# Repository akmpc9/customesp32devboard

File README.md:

# customesp32devboard
# Custom ESP32-S3 Dev Board (v1)

A custom **ESP32-S3** development board designed to be **reliable**, **good-quality**, and **feature-rich** for **learning + teaching electronics** (power, USB, routing, GPIO, LEDs/buttons, battery monitoring).

---

## Images

---

## Project goals

- Make a **robust ESP32-S3 platform** (clean power + clean layout)
- Break out lots of GPIO for experiments
- Add useful learning features (LEDs, buttons, battery sense, USB programming)
- Be easy to reproduce and improve (v1 → v2)

---

## Key features (v1)

- **ESP32-S3-WROOM-1** module (Wi-Fi + BLE)
- **USB-C** connector
- **CH340C** USB-UART for flashing/serial
- **5V → 3.3V buck converter** (efficient vs linear regulators)
- **Auto-program** support (EN/BOOT control from USB-UART)
- **GPIO headers** for prototyping
- **User button** + indicator LEDs
- **Battery sense divider** (read VBAT on an ADC pin)
- Layout rules applied: antenna keepout, USB routing, buck SW isolation, ground plane

---

## Flashing / serial

- Plug USB-C into your PC
- Select the **CH340** COM port
- Use Arduino IDE or PlatformIO (ESP32-S3 target)

---

## BOM (JLCPCB Assembly Order)
I removed the esp32 chip and the leds for a more economical PCBA.

**Build qty:** 5 PCBs (inferred from U1/U2/U3/J1 qty = 5)  
**Parts cost (from JLC export, parts only):** **$60.8676** (assembly + PCB + shipping not included)

Legend: 🟦 Basic | 🟧 Extended | ⚠️ Check

---

<details open>
<summary><b>MCU</b></summary>

| Designators | Qty | Value | Footprint | LCSC | Manufacturer | Lib | Link | Notes |
|---|---:|---|---|---|---|---|---|---|
| U1 | 5 | ESP32-S3-WROOM-1 | RF_Module:ESP32-S3-WROOM-1 | C2913202 | Espressif Systems | 🟧 | https://jlcpcb.com/partdetail/3198300-ESP32_S3_WROOM_1N16R8/C2913202 | ⚠️ Comment mismatch in export |
</details>

<details open>
<summary><b>USB / Interface</b></summary>

| Designators | Qty | Value | Footprint | LCSC | Manufacturer | Lib | Link | Notes |
|---|---:|---|---|---|---|---|---|---|
| J1 | 5 | TYPE-C-31-M-12 | TYPE-C-31-M-12:HRO_TYPE-C-31-M-12 | C165948 | Korean Hroparts Elec | 🟧 | https://jlcpcb.com/partdetail/Korean_HropartsElec-TYPE_C_31_M12/C165948 |  |
| U2 | 5 | CH340C | Package_SO:SOIC-16_3.9x9.9mm_P1.27mm | C7464026 | WCH(Jiangsu Qin Heng) | 🟧 | https://jlcpcb.com/partdetail/WCH_Jiangsu_Qin_Heng-CH340C/C7464026 |  |
| D2,D3,D4 | 21 | LESD5D5.0CT1G | LESD5D5.0CT1G:TVS_LESD5D5.0CT1G | C5199850 | UMW(Youtai) | 🟧 | https://jlcpcb.com/partdetail/5885882-LESD5D5_0CT1G_UMW/C5199850 | ⚠️ Comment mismatch in export |
</details>

<details open>
<summary><b>Power (Buck)</b></summary>

| Designators | Qty | Value | Footprint | LCSC | Manufacturer | Lib | Link | Notes |
|---|---:|---|---|---|---|---|---|---|
| U3 | 5 | MP2303ADN | Package_SO:SOIC-8-1EP_3.9x4.9mm_P1.27mm_EP2.62x3.51mm | C18876 | Monolithic Power Systems | 🟧 | https://jlcpcb.com/partdetail/19579-MP2303ADN_LFZ/C18876 |  |
| L1 | 9 | 4.7uH | Inductor_SMD:L_Sunlord_SWPA4012S | C316363 | Sunlord | 🟧 | https://jlcpcb.com/partdetail/Sunlord-SWPA4012S4R7MT/C316363 |  |
| D1 | 15 | 1N5819HW-7-F | Diode_SMD:D_SOD-123 | C82544 | Diodes Incorporated | 🟧 | https://jlcpcb.com/partdetail/DiodesIncorporated-1N5819HW_7F/C82544 |  |
| RTOP1 | 20 | 26.1k | Resistor_SMD:R_0603_1608Metric | C325725 | TyoHM | 🟧 | https://jlcpcb.com/partdetail/TyoHM-RMC060326_1K1N/C325725 | ⚠️ Comment mismatch in export |
| RCOMP1 | 20 | 12k | Resistor_SMD:R_0603_1608Metric | C22790 | UNI-ROYAL | 🟦 | https://jlcpcb.com/partdetail/23517-0603WAF1202T5E/C22790 |  |
| CCOMP1 | 20 | 3.9nF | Capacitor_SMD:C_0603_1608Metric | C1618 | FH | 🟧 | https://jlcpcb.com/partdetail/1970-0603B392K500NT/C1618 |  |
| CSS1 | 20 | 10nF | Capacitor_SMD:C_0603_1608Metric | C57112 | FH | 🟦 | https://jlcpcb.com/partdetail/58143-0603B103K500NT/C57112 |  |
</details>

<details open>
<summary><b>Passives (Caps)</b></summary>

| Designators | Qty | Value | Footprint | LCSC | Manufacturer | Lib | Link | Notes |
|---|---:|---|---|---|---|---|---|---|
| C1 | 20 | 1uF | Capacitor_SMD:C_0603_1608Metric | C15849 | Samsung EM | 🟦 | https://jlcpcb.com/partdetail/16531-CL10A105KB8NNNC/C15849 |  |
| C2,C4,C6,CBST1,CCH340C1,CCH340C2,CIN2,CLED1,CLED2 | 55 | 100nF | Capacitor_SMD:C_0603_1608Metric | C14663 | YAGEO | 🟦 | https://jlcpcb.com/partdetail/YAGEO-CC0603KRX7R9BB104/C14663 | ⚠️ “multiple types” warning in export |
| C3,CIN1,COUT1,COUT2 | 24 | 22uF | Capacitor_SMD:C_1206_3216Metric | C12891 | Samsung EM | 🟦 | https://jlcpcb.com/partdetail/13537-CL31A226KAHNNNE/C12891 | ⚠️ “multiple types” warning in export |
| C5 | 20 | 10uF | Capacitor_SMD:C_0603_1608Metric | C19702 | Samsung EM | 🟦 | https://jlcpcb.com/partdetail/20411-CL10A106KP8NNNC/C19702 |  |
</details>

<details open>
<summary><b>Passives (Resistors)</b></summary>

| Designators | Qty | Value | Footprint | LCSC | Manufacturer | Lib | Link | Notes |
|---|---:|---|---|---|---|---|---|---|
| R1,R2 | 20 | 5k1 | Resistor_SMD:R_0603_1608Metric | C23186 | UNI-ROYAL | 🟦 | https://jlcpcb.com/partdetail/23913-0603WAF5101T5E/C23186 | ⚠️ Comment mismatch in export |
| R3,R7 | 20 | 10k | Resistor_SMD:R_0805_2012Metric | C17414 | UNI-ROYAL | 🟦 | https://jlcpcb.com/partdetail/18102-0805W8F1002T5E/C17414 | ⚠️ Comment mismatch in export |
| R5,R6 | 20 | 4.7k | Resistor_SMD:R_0603_1608Metric | C23162 | UNI-ROYAL | 🟦 | https://jlcpcb.com/partdetail/23889-0603WAF4701T5E/C23162 | ⚠️ Comment mismatch in export |
| R8,R9,R12,RBOT1 | 30 | 10k | Resistor_SMD:R_0603_1608Metric | C25804 | UNI-ROYAL | 🟦 | https://jlcpcb.com/partdetail/26547-0603WAF1002T5E/C25804 | ⚠️ Warnings in export |
| R10,R11 | 20 | 100k | Resistor_SMD:R_0603_1608Metric | C25803 | UNI-ROYAL | 🟦 | https://jlcpcb.com/partdetail/26546-0603WAF1003T5E/C25803 | ⚠️ Comment mismatch in export |
| RLED1,RLED2 | 20 | 330R | Resistor_SMD:R_0603_1608Metric | C23138 | UNI-ROYAL | 🟦 | https://jlcpcb.com/partdetail/23865-0603WAF3300T5E/C23138 | ⚠️ Use **330R** in BOM to avoid LED auto-match |
| RLED3 | 20 | 3.3k | Resistor_SMD:R_0603_1608Metric | C22978 | UNI-ROYAL | 🟦 | https://jlcpcb.com/partdetail/23705-0603WAF3301T5E/C22978 |  |
</details>

<details open>
<summary><b>LEDs / Indicators</b></summary>

| Designators | Qty | Value | Footprint | LCSC | Manufacturer | Lib | Link | Notes |
|---|---:|---|---|---|---|---|---|---|
| D5,D6 | 12 | SK6805 | LED_SMD:LED_SK6805_PLCC4_2.4x2.7mm_P1.3mm | C2890035 | OPSCO | 🟧 | https://jlcpcb.com/partdetail/OPSCOOptoelectronics-SK6805EC15/C2890035 | ⚠️ Comment mismatch in export |
| D7 | 20 | SM0603UYC | SM0603UYC:LED_SM0603UYC | C2287 | Hubei KENTO | 🟧 | https://jlcpcb.com/partdetail/Hubei_KENTOElec-KT0603Y/C2287 | ⚠️ Comment mismatch in export |
</details>

<details open>
<summary><b>Discrete / Switches</b></summary>

| Designators | Qty | Value | Footprint | LCSC | Manufacturer | Lib | Link | Notes |
|---|---:|---|---|---|---|---|---|---|
| Q1,Q2 | 15 | MMBT3904 | Package_TO_SOT_SMD:SOT-23 | C7420353 | hongjiacheng | 🟧 | https://jlcpcb.com/partdetail/hongjiacheng-MMBT3904/C7420353 |  |
| S1,S2,S3 | 19 | TS-1088-AR02016 | TS-1088-AR02016:SW_TS-1088-AR02016 | C720477 | XUNPU | 🟦 | https://jlcpcb.com/partdetail/XUNPU-TS_1088AR02016/C720477 |  |
</details>

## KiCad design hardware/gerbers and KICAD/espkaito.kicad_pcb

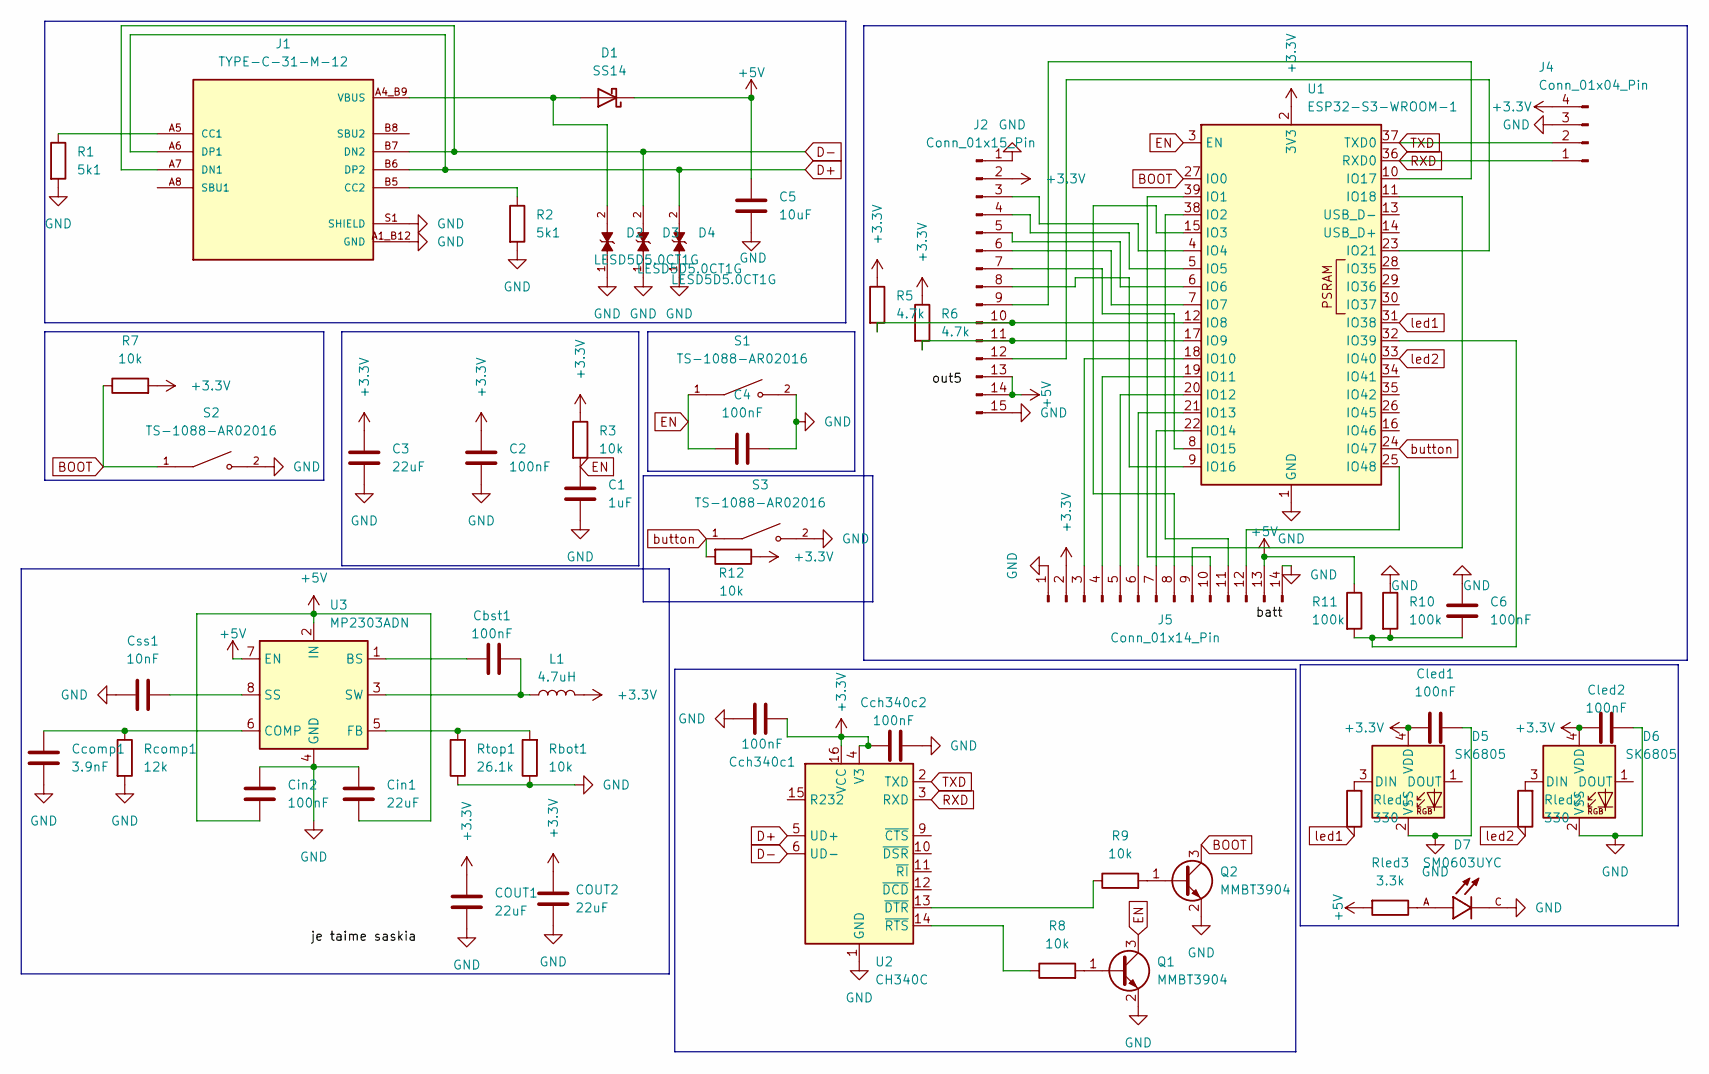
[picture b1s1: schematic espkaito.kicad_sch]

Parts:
C1: 1uF; C_0603_1608Metric
C2, C4, C6: 100nF; C_0603_1608Metric
C3: 22uF; C_1206_3216Metric
C5: 10uF; C_0603_1608Metric
COUT1, COUT2: 22uF; C_1206_3216Metric
Cbst1: 100nF; C_0603_1608Metric
Cch340c1, Cch340c2: 100nF; C_0603_1608Metric
Ccomp1: 3.9nF; C_0603_1608Metric
Cin1: 22uF; C_1206_3216Metric
Cin2: 100nF; C_0603_1608Metric
Cled1, Cled2: 100nF; C_0603_1608Metric
Css1: 10nF; C_0603_1608Metric
D1: SS14; D_SMA
D2, D3, D4: LESD5D5.0CT1G; TVS_LESD5D5.0CT1G; PARTREV O
D5, D6: SK6805; LED_SK6805_PLCC4_2.4x2.7mm_P1.3mm
D7: SM0603UYC; LED_SM0603UYC; PARTREV A
J1: TYPE-C-31-M-12; HRO_TYPE-C-31-M-12; PARTREV 2020.12.08
J2: Conn_01x15_Pin; PinHeader_1x15_P2.54mm_Vertical
J4: Conn_01x04_Pin; PinHeader_1x04_P2.54mm_Vertical
J5: Conn_01x14_Pin; PinHeader_1x14_P2.54mm_Vertical
L1: 4.7uH; L_Sunlord_SWPA4012S
Q1, Q2: MMBT3904; SOT-23
R1, R2: 5k1; R_0603_1608Metric
R3, R7: 10k; R_0805_2012Metric
R5, R6: 4.7k; R_0603_1608Metric
R8, R9, R12: 10k; R_0603_1608Metric
R10, R11: 100k; R_0603_1608Metric
Rbot1: 10k; R_0603_1608Metric
Rcomp1: 12k; R_0603_1608Metric
Rled1, Rled2: 330; R_0603_1608Metric
Rled3: 3.3k; R_0603_1608Metric
Rtop1: 26.1k; R_0603_1608Metric
S1, S2, S3: TS-1088-AR02016; SW_TS-1088-AR02016; PARTREV N/A
U1: ESP32-S3-WROOM-1
U2: CH340C; SOIC-16_3.9x9.9mm_P1.27mm
U3: MP2303ADN; SOIC-8-1EP_3.9x4.9mm_P1.27mm_EP2.62x3.51mm_ThermalVias

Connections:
+3.3V: C2.1, C3.1, COUT1.1, COUT2.1, Cch340c1.2, Cch340c2.2, Cled1.2, Cled2.2, D5.4 (VDD), D6.4 (VDD), J2.2, J4.4, J5.2, L1.2, R3.1, R5.1, R6.1, R7.2, R12.1, U1.2 (3V3), U2.4 (V3), U2.16 (VCC)
+5V: C5.1, Cin1.2, Cin2.1, D1.1 (K), J2.13, J2.14, J5.13, R11.1, Rled3.2, U3.2 (IN), U3.7 (EN)
BOOT: Q2.3 (C), R7.1, S2.1, U1.27 (IO0)
D+: D4.2, J1.A6 (DP1), J1.B6 (DP2), U2.5 (UD+)
D-: D3.2, J1.A7 (DN1), J1.B7 (DN2), U2.6 (UD-)
EN: C1.1, C4.1, Q1.3 (C), R3.2, S1.1, U1.3 (EN)
GND: C1.2, C2.2, C3.2, C4.2, C5.2, C6.1, COUT1.2, COUT2.2, Cch340c1.1, Cch340c2.1, Ccomp1.2, Cin1.1, Cin2.2, Cled1.1, Cled2.1, Css1.1, D2.1, D3.1, D4.1, D5.2 (VSS), D6.2 (VSS), D7.C, J1.A1_B12 (GND), J1.B1_A12 (GND), J1.S1 (SHIELD), J1.S2 (SHIELD), J1.S3 (SHIELD), J1.S4 (SHIELD), J2.1, J2.15, J4.3, J5.1, J5.14, Q1.2 (E), Q2.2 (E), R1.2, R2.2, R10.1, Rbot1.1, Rcomp1.2, Rtop1.1, S1.2, S2.2, S3.2, U1.1 (GND), U1.40 (GND), U1.41 (GND), U2.1 (GND), U3.4 (GND)
unnamed: D5.3 (DIN), Rled1.2
unnamed: D6.3 (DIN), Rled2.2
unnamed: D7.A, Rled3.1
unnamed: J1.A5 (CC1), R1.1
unnamed: J1.B5 (CC2), R2.1
unnamed: J2.3, U1.4 (IO4)
unnamed: J2.4, U1.5 (IO5)
unnamed: J2.5, U1.6 (IO6)
unnamed: J2.6, U1.7 (IO7)
unnamed: J2.7, U1.8 (IO15)
unnamed: J2.8, U1.9 (IO16)
unnamed: J2.9, U1.10 (IO17)
unnamed: J2.10, R5.2, U1.12 (IO8)
unnamed: J2.11, R6.2, U1.17 (IO9)
unnamed: J2.12, U1.23 (IO21)
unnamed: J5.3, U1.18 (IO10)
unnamed: J5.4, U1.19 (IO11)
unnamed: J5.5, U1.20 (IO12)
unnamed: J5.6, U1.21 (IO13)
unnamed: J5.7, U1.22 (IO14)
unnamed: J5.8, U1.15 (IO3)
unnamed: J5.9, U1.11 (IO18)
unnamed: J5.10, U1.39 (IO1)
unnamed: J5.11, U1.38 (IO2)
unnamed: J5.12, U1.25 (IO48)
unnamed: Q1.1 (B), R8.2
unnamed: Q2.1 (B), R9.2
unnamed: C6.2, R10.2, R11.2, U1.32 (IO39)
unnamed: R9.1, U2.13 (~DTR)
unnamed: R8.1, U2.14 (~RTS)
unnamed: Cbst1.2, U3.1 (BS)
unnamed: Ccomp1.1, Rcomp1.1, U3.6 (COMP)
unnamed: Rbot1.2, Rtop1.2, U3.5 (FB)
unnamed: Css1.2, U3.8 (SS)
unnamed: Cbst1.1, L1.1, U3.3 (SW)
RXD: J4.1, U1.36 (RXD0), U2.3 (RXD)
TXD: J4.2, U1.37 (TXD0), U2.2 (TXD)
VBUS: D1.2 (A), D2.2, J1.A4_B9 (VBUS), J1.B4_A9 (VBUS)
button: R12.2, S3.1, U1.24 (IO47)
led1: Rled1.1, U1.31 (IO38)
led2: Rled2.1, U1.33 (IO40)

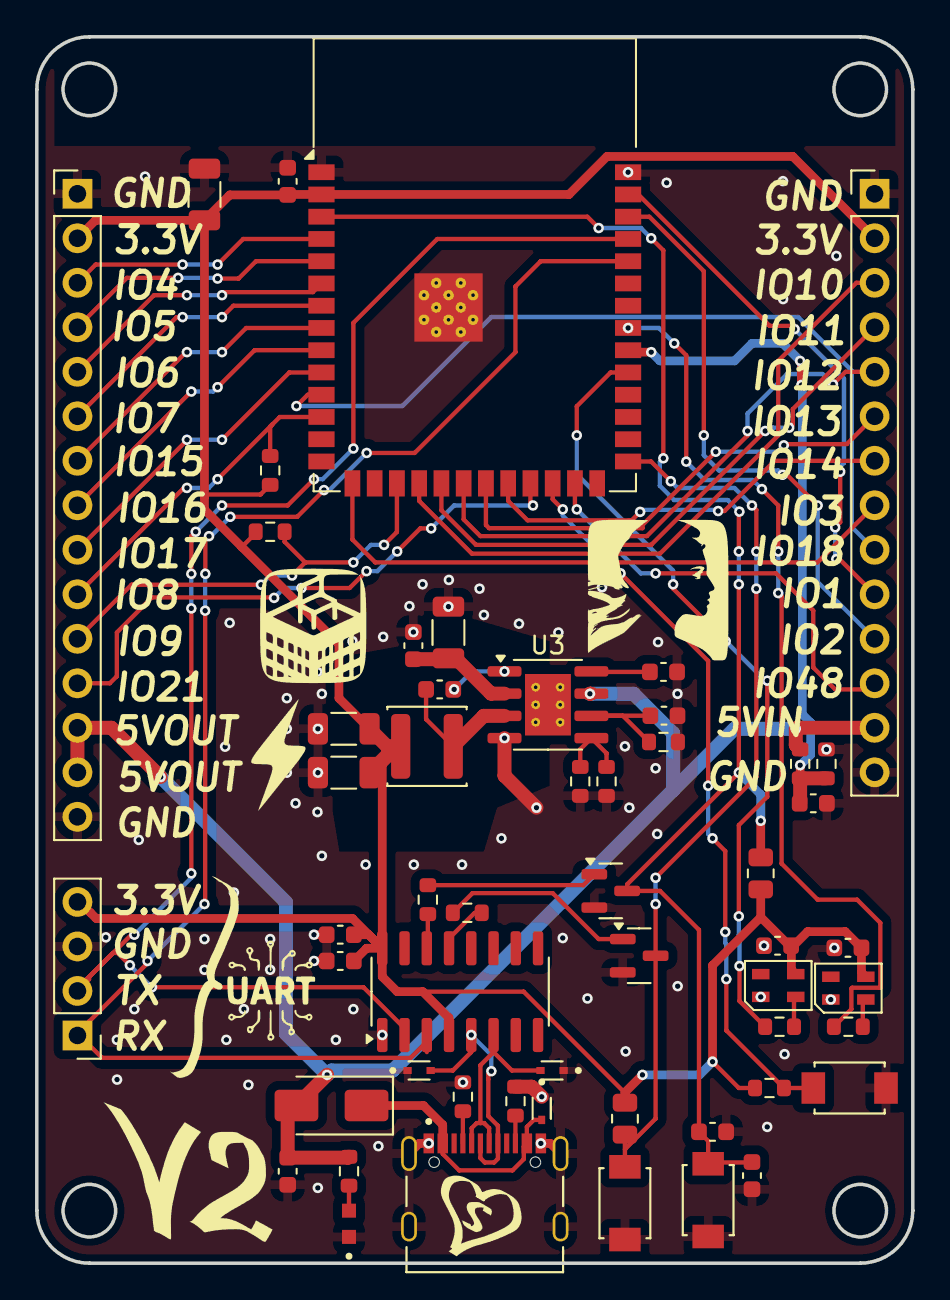
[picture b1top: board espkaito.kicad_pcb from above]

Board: 2 copper layers, 50.0 x 70.0 mm, 54 parts (0 on the bottom side), 48 nets.

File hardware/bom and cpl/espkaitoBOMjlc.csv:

"Reference","Qty","Value","DNP","Exclude from BOM","Exclude from Board","Footprint","Datasheet"
"C1","1","1uF","","","","Capacitor_SMD:C_0603_1608Metric","~"
"C2,C4,C6,Cbst1,Cch340c1,Cch340c2,Cin2,Cled1,Cled2","9","100nF","","","","Capacitor_SMD:C_0603_1608Metric","~"
"C3,Cin1,COUT1,COUT2","4","22uF","","","","Capacitor_SMD:C_1206_3216Metric","~"
"C5","1","10uF","","","","Capacitor_SMD:C_0603_1608Metric","~"
"Ccomp1","1","3.9nF","","","","Capacitor_SMD:C_0603_1608Metric","~"
"Css1","1","10nF","","","","Capacitor_SMD:C_0603_1608Metric","~"
"D1","1","1N5819HW-7-F","","","","Diode_SMD:D_SOD-123",""
"D2,D3,D4","3","LESD5D5.0CT1G","","","","LESD5D5.0CT1G:TVS_LESD5D5.0CT1G",""
"D5,D6","2","SK6805","","","","LED_SMD:LED_SK6805_PLCC4_2.4x2.7mm_P1.3mm","https://cdn-shop.adafruit.com/product-files/3484/3484_Datasheet.pdf"
"D7","1","SM0603UYC","","","","SM0603UYC:LED_SM0603UYC",""
"J1","1","TYPE-C-31-M-12","","","","TYPE-C-31-M-12:HRO_TYPE-C-31-M-12",""
"J2","1","Conn_01x15_Pin","","","","Connector_PinHeader_2.54mm:PinHeader_1x15_P2.54mm_Vertical","~"
"J4","1","Conn_01x04_Pin","","","","Connector:FanPinHeader_1x04_P2.54mm_Vertical","~"
"J5","1","Conn_01x14_Pin","","","","Connector_PinHeader_2.54mm:PinHeader_1x14_P2.54mm_Vertical","~"
"L1","1","4.7uH","","","","Inductor_SMD:L_Sunlord_SWPA4012S","~"
"Q1,Q2","2","MMBT3904","","","","Package_TO_SOT_SMD:SOT-23","https://www.onsemi.com/pdf/datasheet/pzt3904-d.pdf"
"R1,R2","2","5k1","","","","Resistor_SMD:R_0603_1608Metric","~"
"R3,R7","2","10k","","","","Resistor_SMD:R_0805_2012Metric","~"
"R5,R6","2","4.7k","","","","Resistor_SMD:R_0603_1608Metric","~"
"R8,R9,R12,Rbot1","4","10k","","","","Resistor_SMD:R_0603_1608Metric","~"
"R10,R11","2","100k","","","","Resistor_SMD:R_0603_1608Metric","~"
"Rcomp1","1","12k","","","","Resistor_SMD:R_0603_1608Metric","~"
"Rled1,Rled2","2","330","","","","Resistor_SMD:R_0603_1608Metric","~"
"Rled3","1","3.3k","","","","Resistor_SMD:R_0603_1608Metric","~"
"Rtop1","1","26.1k","","","","Resistor_SMD:R_0603_1608Metric","~"
"S1,S2,S3","3","TS-1088-AR02016","","","","TS-1088-AR02016:SW_TS-1088-AR02016",""
"U1","1","ESP32-S3-WROOM-1","","","","RF_Module:ESP32-S3-WROOM-1","https://www.espressif.com/sites/default/files/documentation/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"
"U2","1","CH340C","","","","Package_SO:SOIC-16_3.9x9.9mm_P1.27mm","https://datasheet.lcsc.com/szlcsc/Jiangsu-Qin-Heng-CH340C_C8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"
"U3","1","MP2303ADN","","","","Package_SO:SOIC-8-1EP_3.9x4.9mm_P1.27mm_EP2.62x3.51mm","https://www.monolithicpower.com/pub/media/document/MP2303A_r1.1.pdf"

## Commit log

2026-02-17 added source
2026-02-20 Rename view.png to docs/view.png
2026-02-20 Rename schematic.png to docs/schematic.png
2026-02-20 Rename route.png to docs/route.png
